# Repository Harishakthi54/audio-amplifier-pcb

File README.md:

View this project on [CADLAB.io](https://cadlab.io/project/29290). 

# audio-amplifier-pcb

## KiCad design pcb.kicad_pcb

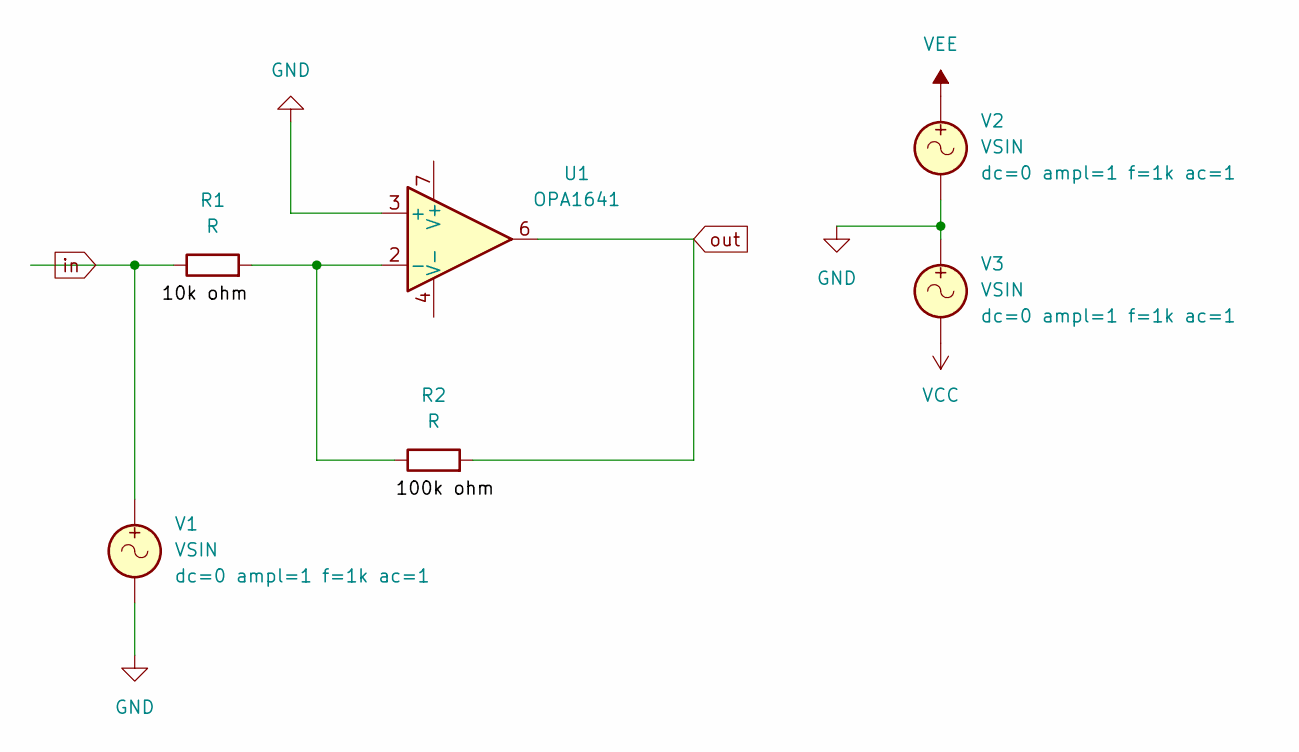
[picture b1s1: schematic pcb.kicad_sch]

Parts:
R1: R; R_LDR_11x9.4mm_P8.2mm_Vertical
R2: R; R_LDR_7x6mm_P5.1mm_Vertical
U1: OPA1641; VSSOP-8_3x3mm_P0.65mm
V1, V2, V3: VSIN; BatteryHolder_ComfortableElectronic_CH273-2450_1x2450

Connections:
GND: U1.3 (+), V1.2, V2.2, V3.1
unnamed: R1.2, R2.1, U1.2 (-)
VCC: V3.2
VEE: V2.1
in: R1.1, V1.1
out: R2.2, U1.6

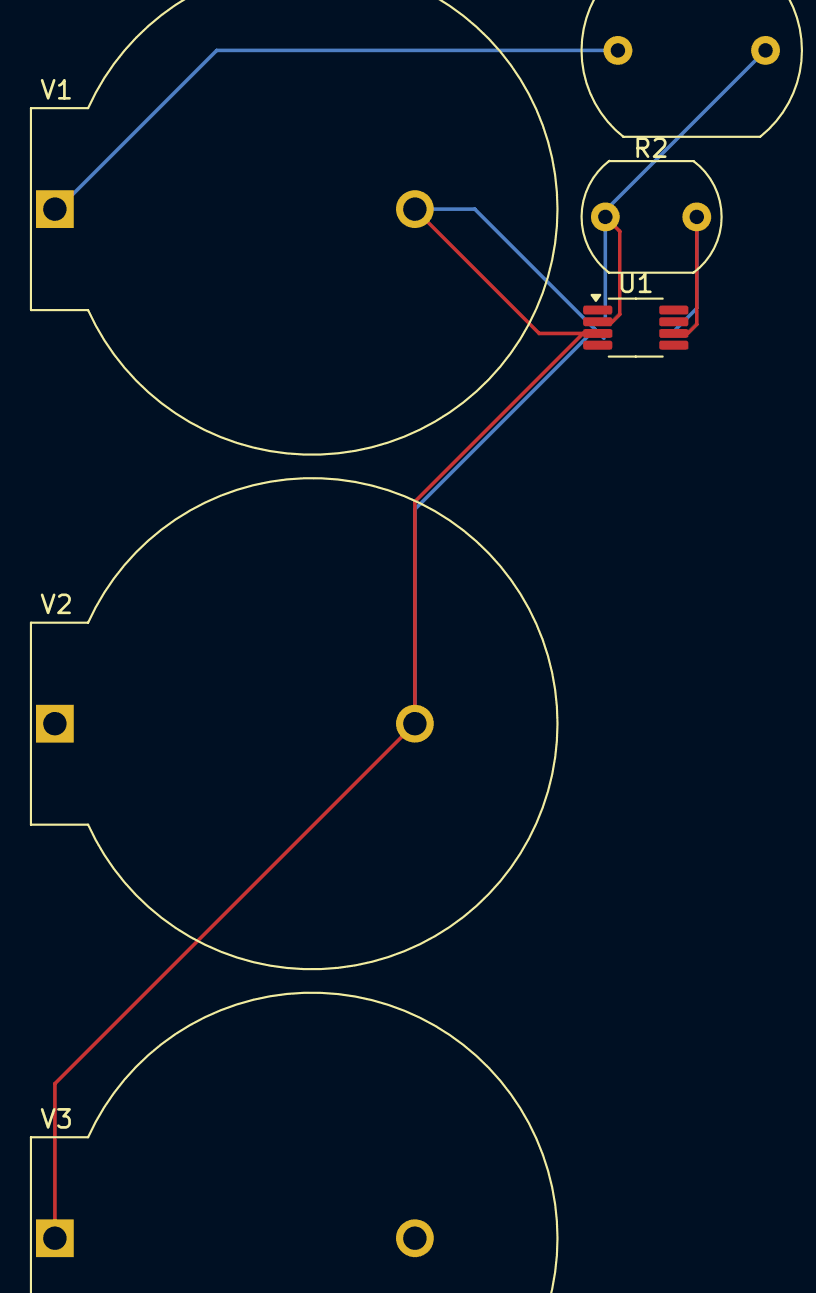
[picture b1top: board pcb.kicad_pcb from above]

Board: 2 copper layers, 6 parts (0 on the bottom side), 4 nets.

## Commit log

2025-04-21 Backlink to CADLAB.io has been added.
